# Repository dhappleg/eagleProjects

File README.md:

# Michgian Tech: Open Source Roller Bottle Apparatus - Circuit design files
> Documents for eagle projects

# Software Used
Software needed to control the arduino and UI for this board. [RollerBottle](https://github.com/dhappleg/RollerBottle)

### Requirements 
* [Autodesk Eagle](https://www.autodesk.com/products/eagle/overview)

## Contributing
Changes to this repo and pull requests are not suggested due to the special use of this design and the underlying project details. 

##Autor 
Drew Applegath

## License
[MIT](https://choosealicense.com/licenses/mit/)
***
_This file was generated by Drew Applegath, v0.0.1, on October 09, 2018._

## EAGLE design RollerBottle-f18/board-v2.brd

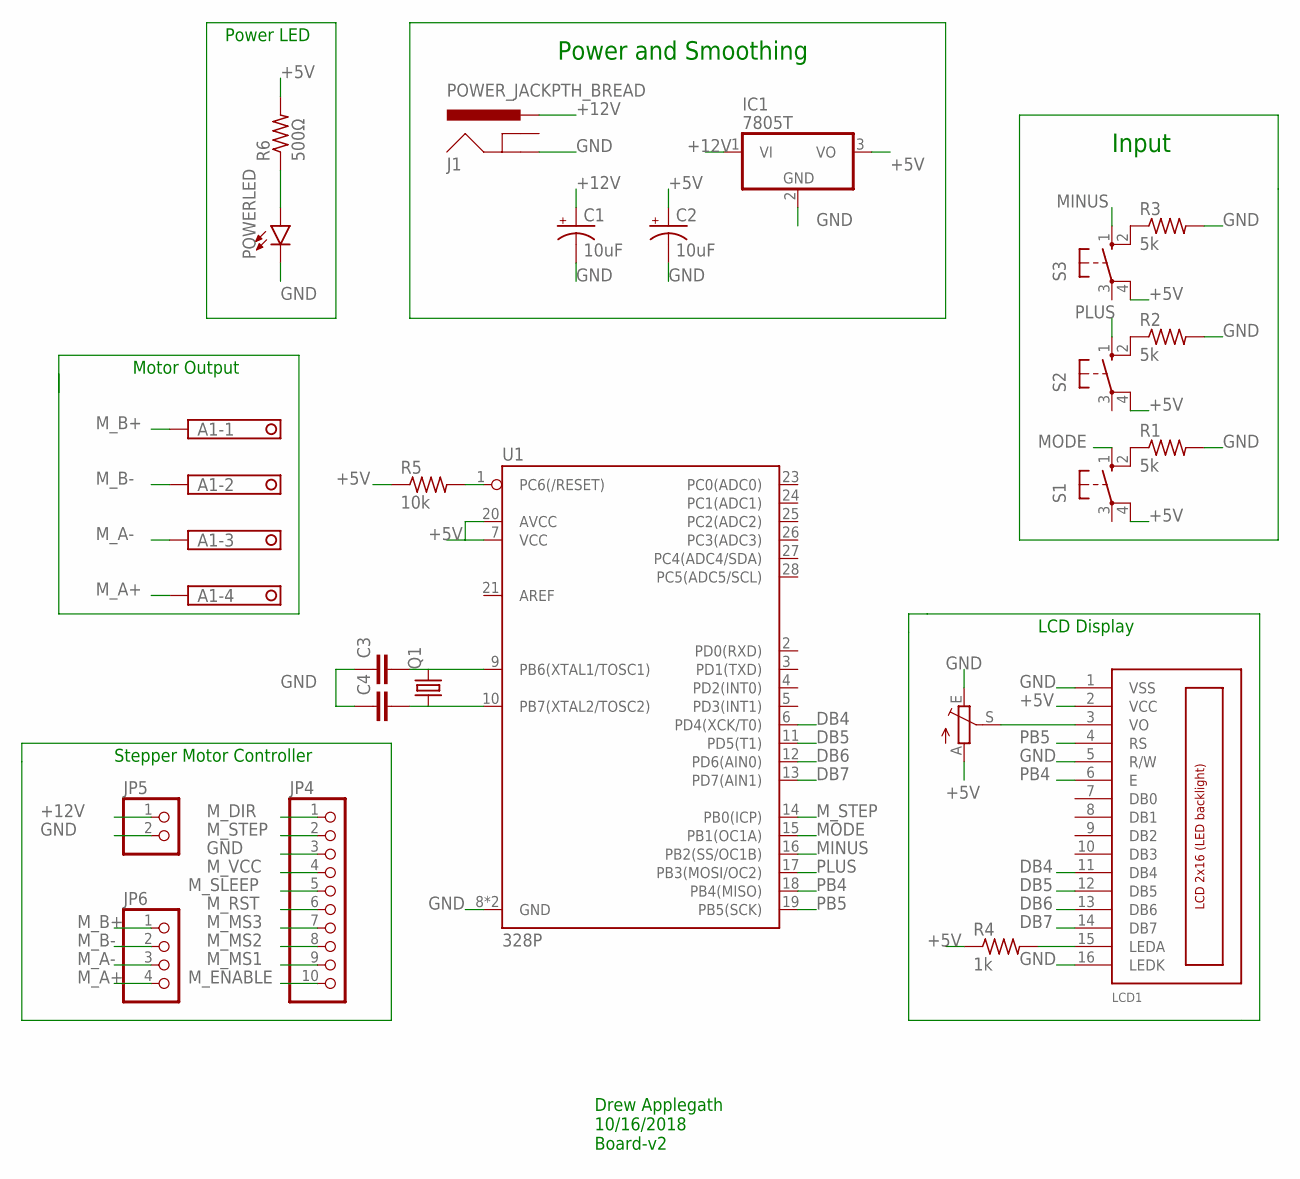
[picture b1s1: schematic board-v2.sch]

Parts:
A1: TERMINAL-BLOCK-3.5MM-4-PIN-LONG-PAD; TERMINAL-BLOCK-4-PIN-3.5MM-LONG-PAD
C1, C2: 10uF; CPOL-RADIAL-2.5MM-5MM
C3, C4: C-EU025-024X044; C025-024X044
IC1: 7805T; TO220H
J1: POWER_JACKPTH_BREAD; POWER_JACK_PTH_BREAD
JP4: PINHD-1X10; 1X10
JP5: PINHD-1X2; 1X02
JP6: PINHD-1X4; 1X04
LCD1: LCD_2X16_SIL; HY-1602F
POWERLED: LED-3MM-NO_SILK; LED_3MM-NS
Q1: CRYSTALHC49S; HC49/S
R1, R2, R3: 5k; 0207/7
R4: 1k; 0207/7
R5: 10k; 0207/7
R6: 500Ω; 0207/7
R7: TRIM_EU-S63S; S63S
S1, S2, S3: 40-XX; B3F-40XX
U1: 328P; DIP28

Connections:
+5V: C2.1 (+), IC1.3 (VO), LCD1.2 (VCC), R4.1, R5.1, R6.2, R7.A, S1.4 (P1), S2.4 (P1), S3.4 (P1), U1.7 (VCC), U1.20 (AVCC)
+12V: C1.1 (+), IC1.1 (VI), J1.PWR, JP5.1
DB4: LCD1.11 (DB4), U1.6 (PD4(XCK/T0))
DB5: LCD1.12 (DB5), U1.11 (PD5(T1))
DB6: LCD1.13 (DB6), U1.12 (PD6(AIN0))
DB7: LCD1.14 (DB7), U1.13 (PD7(AIN1))
GND: C1.2 (-), C2.2 (-), C3.1, C4.1, IC1.2 (GND), J1.GND, JP4.3, JP5.2, LCD1.1 (VSS), LCD1.5 (R/W), LCD1.16 (LEDK), POWERLED.K (C), R1.2, R2.2, R3.2, R7.E, U1.8 (GND), U1.22 (GND)
MINUS: S3.1 (S), U1.16 (PB2(SS/OC1B))
MODE: S1.1 (S), U1.15 (PB1(OC1A))
M_A+: A1.4, JP6.4
M_A-: A1.3, JP6.3
M_B+: A1.1, JP6.1
M_B-: A1.2, JP6.2
M_DIR: JP4.1
M_ENABLE: JP4.10
M_MS1: JP4.9
M_MS2: JP4.8
M_MS3: JP4.7
M_RST: JP4.6
M_SLEEP: JP4.5
M_STEP: JP4.2, U1.14 (PB0(ICP))
M_VCC: JP4.4
unnamed: C4.2, Q1.1, U1.10 (PB7(XTAL2/TOSC2))
unnamed: LCD1.3 (VO), R7.S
unnamed: R5.2, U1.1 (PC6(/RESET))
unnamed: LCD1.15 (LEDA), R4.2
unnamed: C3.2, Q1.2, U1.9 (PB6(XTAL1/TOSC1))
unnamed: R1.1, S1.2 (S1)
unnamed: R2.1, S2.2 (S1)
unnamed: R3.1, S3.2 (S1)
unnamed: POWERLED.A, R6.1
PB4: LCD1.6 (E), U1.18 (PB4(MISO))
PB5: LCD1.4 (RS), U1.19 (PB5(SCK))
PLUS: S2.1 (S), U1.17 (PB3(MOSI/OC2))

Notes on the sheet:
Power and Smoothing
Input
Power LED
Stepper Motor Controller
Motor Output
LCD Display
Drew Applegath 10/16/2018 Board-v2

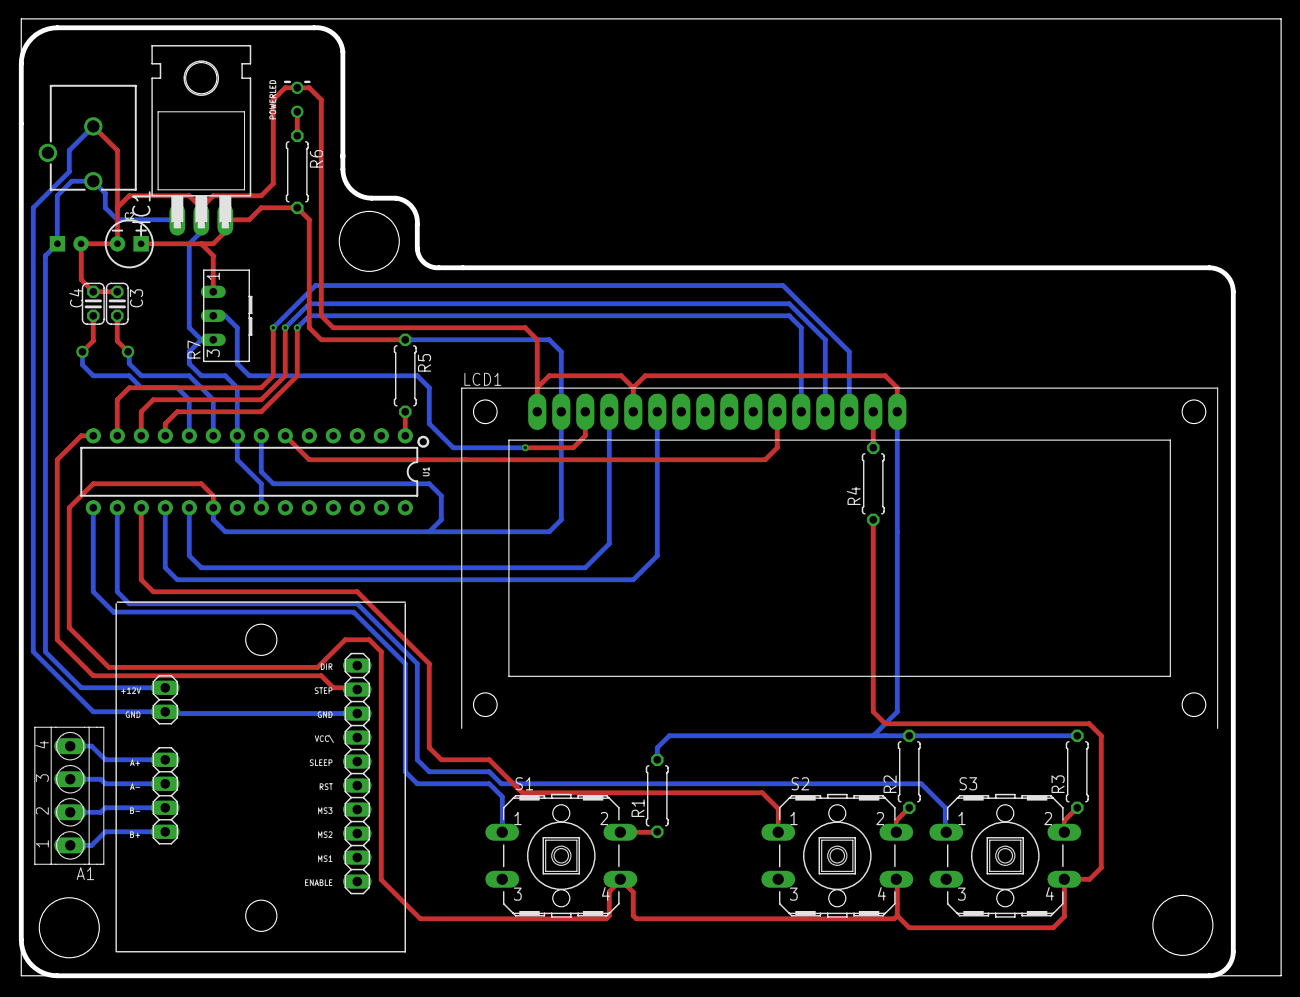
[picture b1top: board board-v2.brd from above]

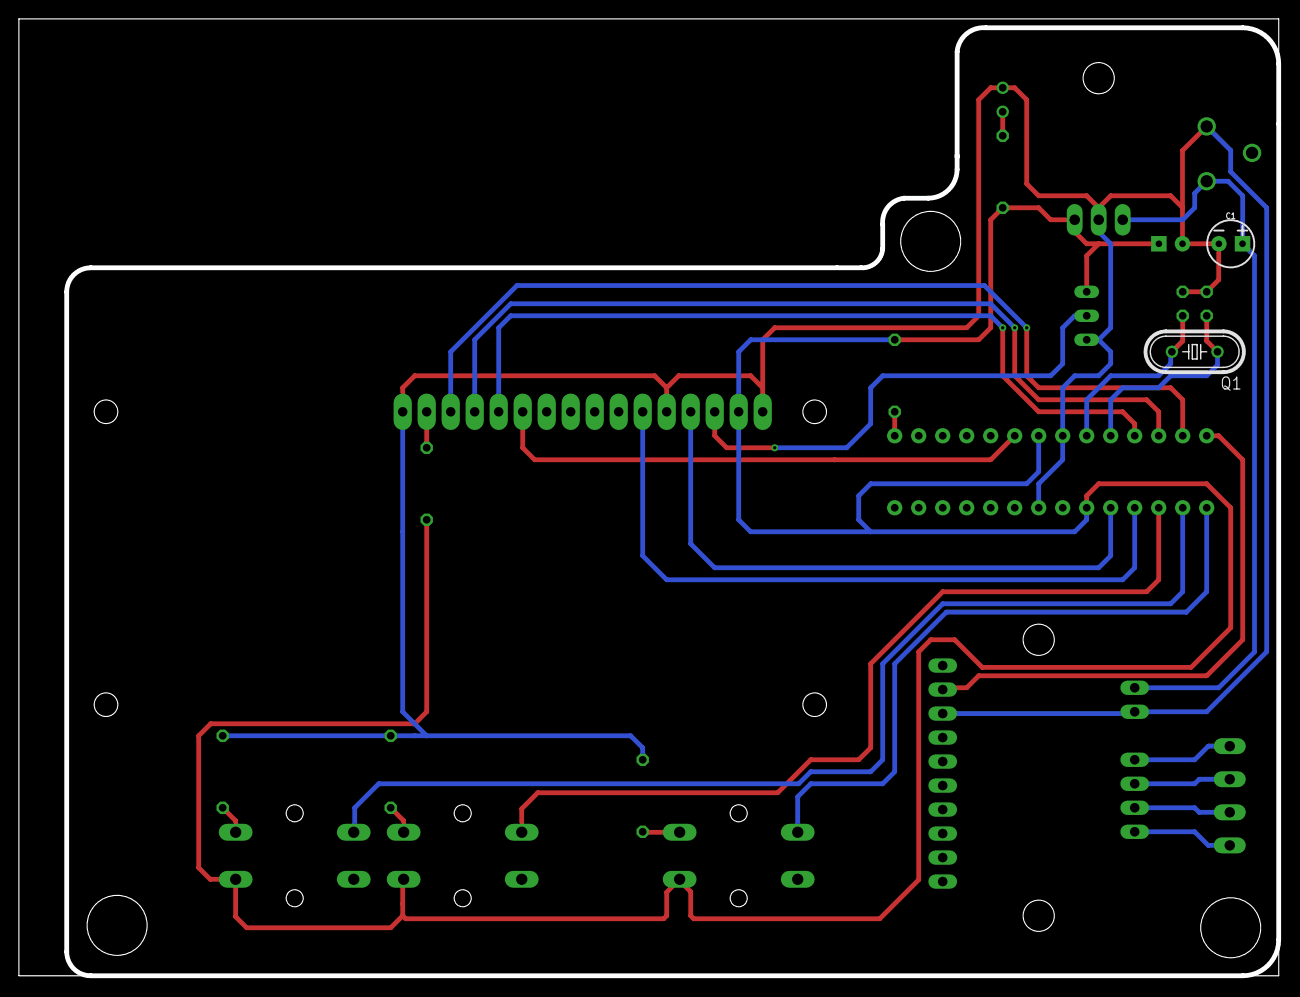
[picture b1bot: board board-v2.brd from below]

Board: 2 copper layers, 133.1 x 101.0 mm, 24 parts (2 on the bottom side), 26 nets.

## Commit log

2018-10-10 Updated Big easy stepper design block and added to board_v2
2018-10-11 Traces added
2018-10-16 Backing up board v2
2018-10-16 Board finished

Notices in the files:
parts and their libraries:
SparkFun-Capacitors: Licensing: Creative Commons ShareAlike 4.0 International - https://creativecommons.org/licenses/by-sa/4.0
